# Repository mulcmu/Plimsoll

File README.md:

# Plimsoll

Prototype designs for klipper load cell ADC implementations.

### Alpha Test

STM32F072 and HX717 based strain gauge for use as a Klipper load cell.

Initial batch ordered for testing with JLCPCB.  About 5.5 USD cost per board.

Firmware and configuration tested with [current community test branch](https://github.com/garethky/klipper/tree/load-cell-probe-community-testing).

Smallish size, 20x50 mm footprint.  M2.5 mounting holes.  Fab house added the smaller tooling holes...

4 layer PCB all parts on top side.

MCU selected for crystal less USB operation with minimum of 64k flash for firmware.

Separate low noise, high PSRR for analog Vdd supply.

HX717 default data rate 320 Hz.  Adjustable with solder jumpers.

> [!NOTE]
>
> Crystal less main clock is problematic with Klipper and maybe the HX717 code.
>
> Works fine 90% of time, but suffers from occasional timeouts during probes.

### Mini HX717 / Mini ADS1220

Addon for a FYSETC H36 **v1** Toolhead board.  Uses the 2x6 2mm expansion pin headers for mounting.  Hardware spi works for the [H36_COMBO](https://wiki.fysetc.com/docs/H36-Combo).  The [H36_COMBO_V2](https://wiki.fysetc.com/docs/H36-Combo-V2) changed the header pins.

Straight needle 2mm 2x6 female pin header (4.3mm plastic body) fits with 6mm standoff but doesn't clear the _IO.0+1_ with a cable installed. A bent needle 2mm 2x6 header works (6mm plastic body) with 8mm standoff after bending the pins to be straight.

4 layer PCB all parts on top side.

Separate low noise, high PSRR for analog Vdd supply.

HX717 data rate 320 Hz.  

Klipper configs for ADS1220/HX717 configs.  
Users have reported __software SPI__ is functional on the v2 boards.

H36 V1
```
sensor_type: ads1220
cs_pin: toolhead:PB6
spi_bus: spi1a
data_ready_pin: toolhead:PC13

sensor_type: hx717
sclk_pin: toolhead:PB3
dout_pin: toolhead:PB4
```

H36 V2
```
sensor_type: ads1220
cs_pin: toolhead:PA14
data_ready_pin: toolhead:PA1
spi_software_sclk_pin:PB7
spi_software_mosi_pin:PB13
spi_software_miso_pin:PA15
spi_speed: 256000

sensor_type: hx717
sclk_pin: toolhead:PB7
dout_pin: toolhead:PA15
```

### 4ch Underbed

4 channel ADS131M04 for underbed applications.  Each load cell can be individually measured and digitally summed.

8.192 MHz clock hardware generator.

Separate low noise, high PSRR for analog Vdd supply.

### Todo:

- [X] Test 2mm pin header fitup on mini pcb
- [x] Test mini ads1220
- [x] Test mini hx717
- [ ] Test underbed pcb
- [ ] ADS131M04 firmware and klipper support

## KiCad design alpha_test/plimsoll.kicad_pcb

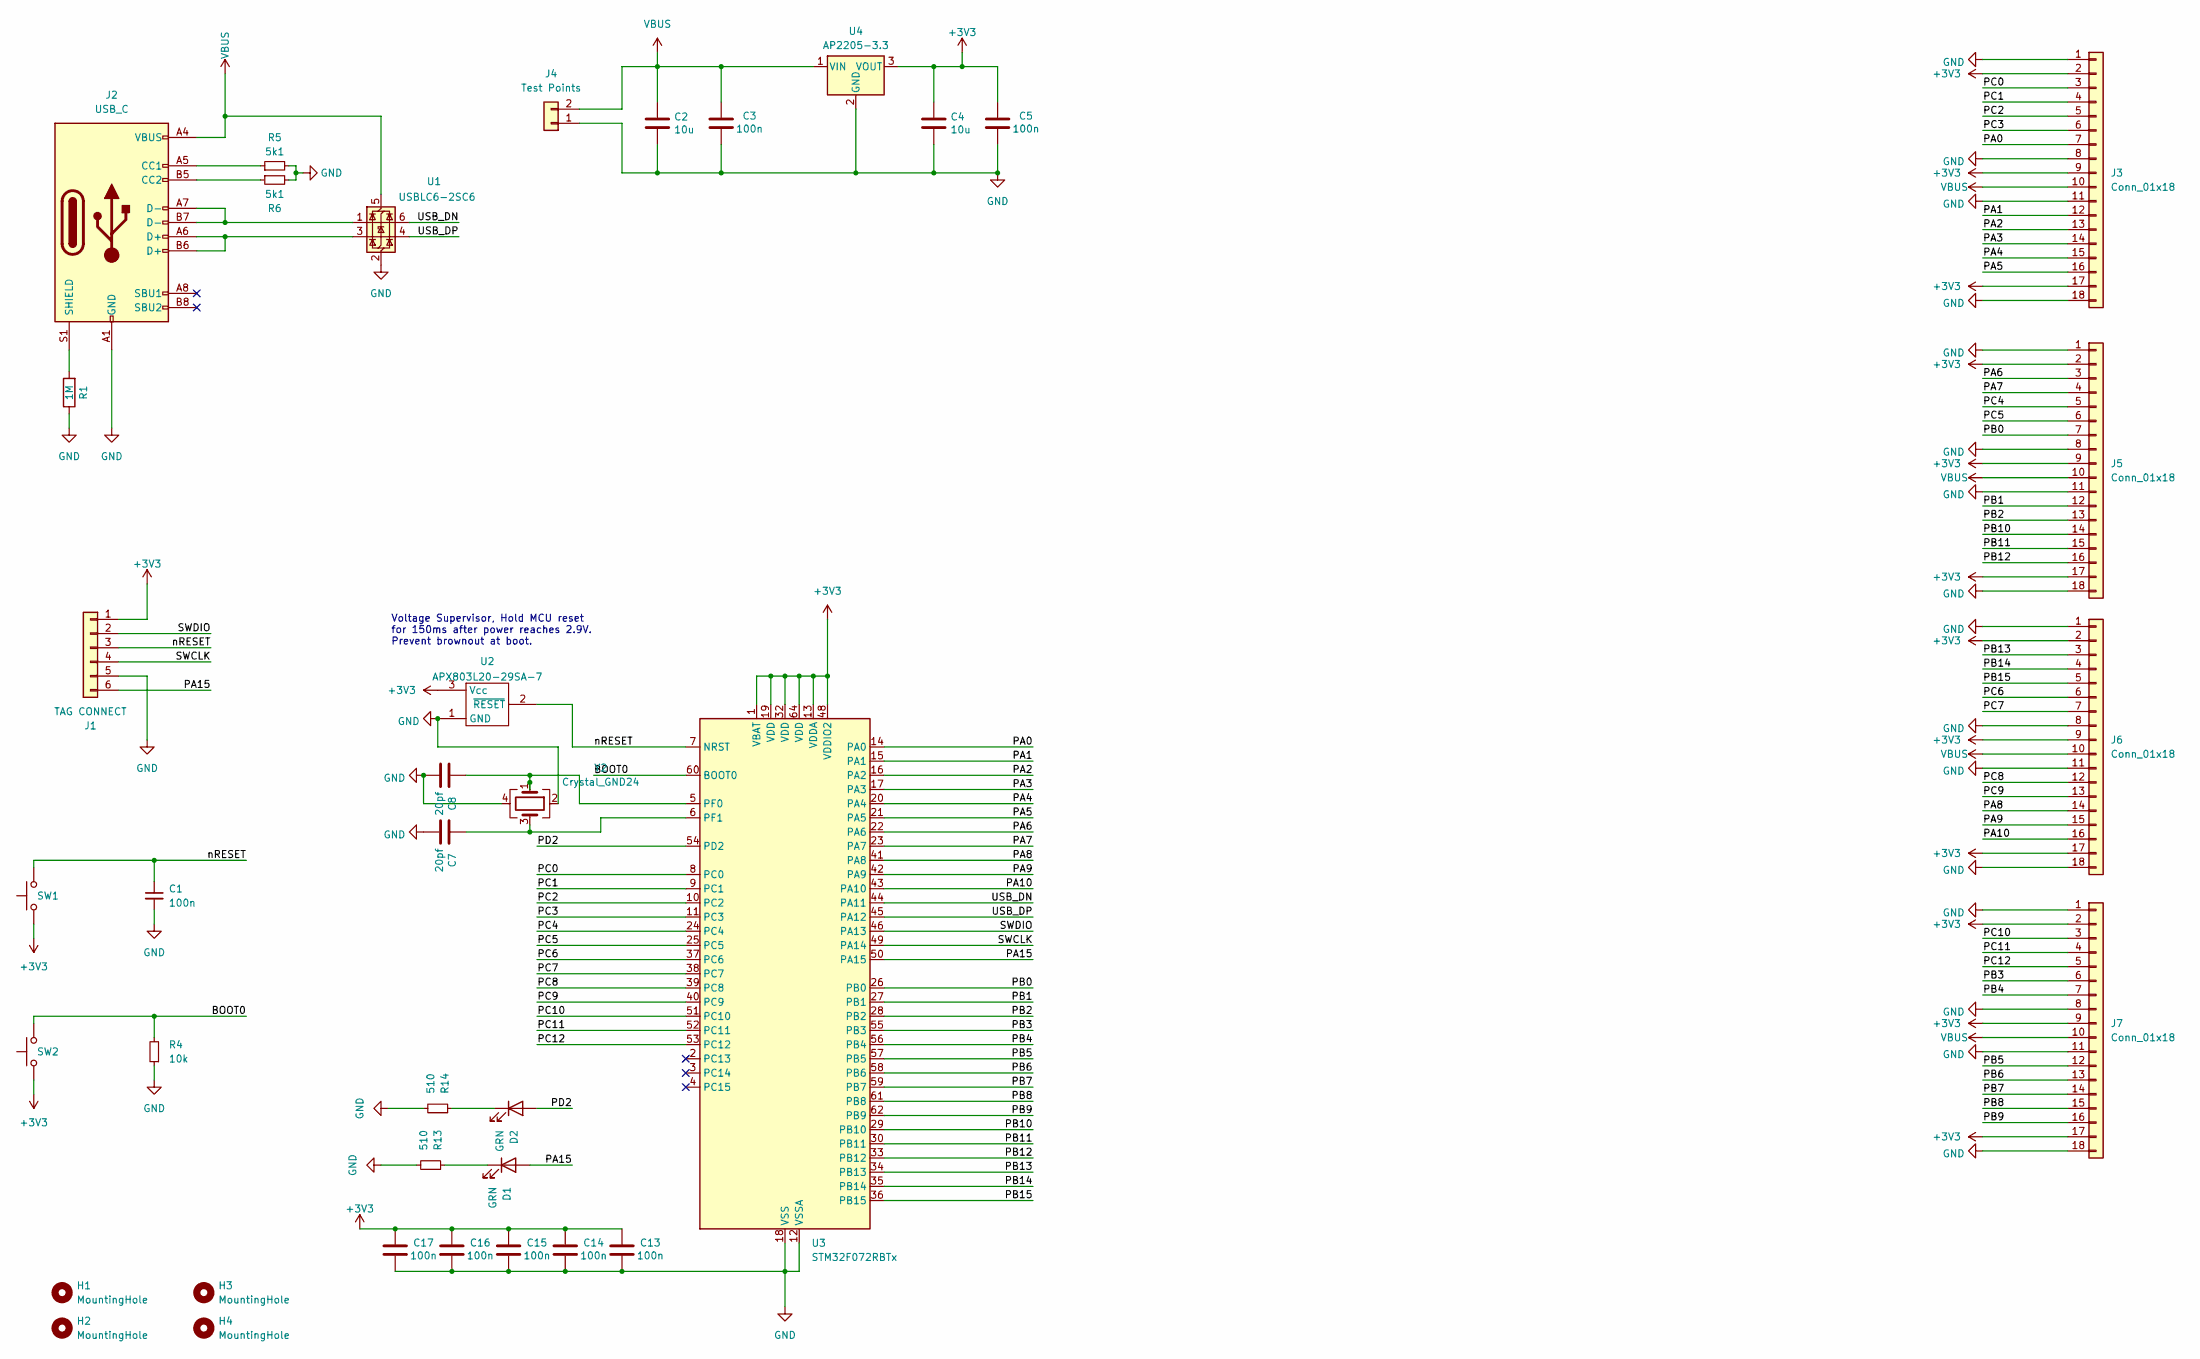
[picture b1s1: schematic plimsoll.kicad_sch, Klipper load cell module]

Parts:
C1, C3, C5, C13, C14, C15, C16, C17: 100n; C_0603_1608Metric; LCSC PN C14663
C2, C4: 10u; C_0805_2012Metric; LCSC PN C15850
C7, C8: 20pf; C_0603_1608Metric; LCSC PN C14663
D1, D2: GRN; LED_0805_2012Metric; LCSC PN C2297
H1, H2, H3, H4: MountingHole; MountingHole_2.2mm_M2_ISO7380
J1: TAG CONNECT; Tag-Connect_TC2030-IDC-NL_2x03_P1.27mm_Vertical
J2: USB_C; USB_C_Receptacle_G-Switch_GT-USB-7010ASV; LCSC PN C2988369
J3, J5, J6, J7: Conn_01x18; PinHeader_1x18_P2.54mm_Vertical
J4: Test Points; PinHeader_1x02_P2.54mm_Vertical
R1: 1M; R_0805_2012Metric; LCSC PN C17514
R4: 10k; R_0603_1608Metric; LCSC PN C25804
R5, R6: 5k1; R_0603_1608Metric; LCSC PN C23186
R13, R14: 510; R_0603_1608Metric; LCSC PN C23193
SW1: RESET; push_button; LCSC PN C720477
SW2: BOOT0; push_button; LCSC PN C720477
U1: USBLC6-2SC6; SOT-23-6; LCSC PN C7519
U2: APX803L20-29SA-7; SOT-23; LCSC PN C2067355
U3: STM32F072RBTx; LQFP-64_10x10mm_P0.5mm; LCSC PN C46046
U4: AP2205-3.3; SOT-89-3; LCSC PN C5205181
Y2: Crystal_GND24; Crystal_SMD_3225-4Pin_3.2x2.5mm_HandSoldering

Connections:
+3V3: C4.1, C5.2, C13.2, C14.2, C15.2, C16.2, C17.2, J1.1, J3.2, J3.9, J3.17, J5.2, J5.9, J5.17, J6.2, J6.9, J6.17, J7.2, J7.9, J7.17, SW1.1, SW2.1, U2.3 (Vcc), U3.1 (VBAT), U3.13 (VDDA), U3.19 (VDD), U3.32 (VDD), U3.48 (VDDIO2), U3.64 (VDD), U4.3 (VOUT); also elsewhere on the board
/BOOT0: R4.2, SW2.2, U3.60 (BOOT0); also elsewhere on the board
/PA0: J3.7, U3.14 (PA0)
/PA1: J3.12, U3.15 (PA1)
/PA2: J3.13, U3.16 (PA2)
/PA3: J3.14, U3.17 (PA3)
/PA4: J3.15, U3.20 (PA4)
/PA5: J3.16, U3.21 (PA5)
/PA6: J5.3, U3.22 (PA6)
/PA7: J5.4, U3.23 (PA7)
/PA8: J6.14, U3.41 (PA8)
/PA9: J6.15, U3.42 (PA9)
/PA10: J6.16, U3.43 (PA10)
/PA15: D1.2 (A), J1.6, U3.50 (PA15)
/PB0: J5.7, U3.26 (PB0)
/PB1: J5.12, U3.27 (PB1)
/PB2: J5.13, U3.28 (PB2)
/PB3: J7.6, U3.55 (PB3)
/PB4: J7.7, U3.56 (PB4)
/PB5: J7.12, U3.57 (PB5)
/PB6: J7.13, U3.58 (PB6)
/PB7: J7.14, U3.59 (PB7)
/PB8: J7.15, U3.61 (PB8)
/PB9: J7.16, U3.62 (PB9)
/PB10: J5.14, U3.29 (PB10)
/PB11: J5.15, U3.30 (PB11)
/PB12: J5.16, U3.33 (PB12)
/PB13: J6.3, U3.34 (PB13)
/PB14: J6.4, U3.35 (PB14)
/PB15: J6.5, U3.36 (PB15)
/PC0: J3.3, U3.8 (PC0)
/PC1: J3.4, U3.9 (PC1)
/PC2: J3.5, U3.10 (PC2)
/PC3: J3.6, U3.11 (PC3)
/PC4: J5.5, U3.24 (PC4)
/PC5: J5.6, U3.25 (PC5)
/PC6: J6.6, U3.37 (PC6)
/PC7: J6.7, U3.38 (PC7)
/PC8: J6.12, U3.39 (PC8)
/PC9: J6.13, U3.40 (PC9)
/PC10: J7.3, U3.51 (PC10)
/PC11: J7.4, U3.52 (PC11)
/PC12: J7.5, U3.53 (PC12)
/PD2: D2.2 (A), U3.54 (PD2)
/SWCLK: J1.4, U3.49 (PA14)
/SWDIO: J1.2, U3.46 (PA13)
/USB_DN: U1.6 (I/O1), U3.44 (PA11)
/USB_DP: U1.4 (I/O2), U3.45 (PA12)
/nRESET: C1.1, J1.3, SW1.2, U2.2 (~RESET), U3.7 (NRST); also elsewhere on the board
GND: C1.2, C2.2, C3.1, C4.2, C5.1, C7.1, C8.1, C13.1, C14.1, C15.1, C16.1, C17.1, J1.5, J2.A1 (GND), J2.A12 (GND), J2.B1 (GND), J2.B12 (GND), J3.1, J3.8, J3.11, J3.18, J4.1, J5.1, J5.8, J5.11, J5.18, J6.1, J6.8, J6.11, J6.18, J7.1, J7.8, J7.11, J7.18, R1.1, R4.1, R5.2, R6.2, R13.2, R14.2, U1.2 (GND), U2.1 (GND), U3.12 (VSSA), U3.18 (VSS), U3.31 (VSS), U3.47 (VSS), U3.63 (VSS), U4.2 (GND), Y2.2, Y2.4
unnamed: D1.1 (K), R13.1
unnamed: D2.1 (K), R14.1
unnamed: J2.A5 (CC1), R5.1
unnamed: J2.B5 (CC2), R6.1
unnamed: J2.A6 (D+), J2.B6 (D+), U1.3 (I/O2)
unnamed: J2.A7 (D-), J2.B7 (D-), U1.1 (I/O1)
unnamed: J2.S1 (SHIELD), R1.2
unnamed: C8.2, U3.5 (PF0), Y2.1
unnamed: C7.2, U3.6 (PF1), Y2.3
VBUS: C2.1, C3.2, J2.A4 (VBUS), J2.A9 (VBUS), J2.B4 (VBUS), J2.B9 (VBUS), J3.10, J4.2, J5.10, J6.10, J7.10, U1.5 (VBUS), U4.1 (VIN)

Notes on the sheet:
Voltage Supervisor, Hold MCU reset for 150ms after power reaches 2.9V. Prevent brownout at boot.

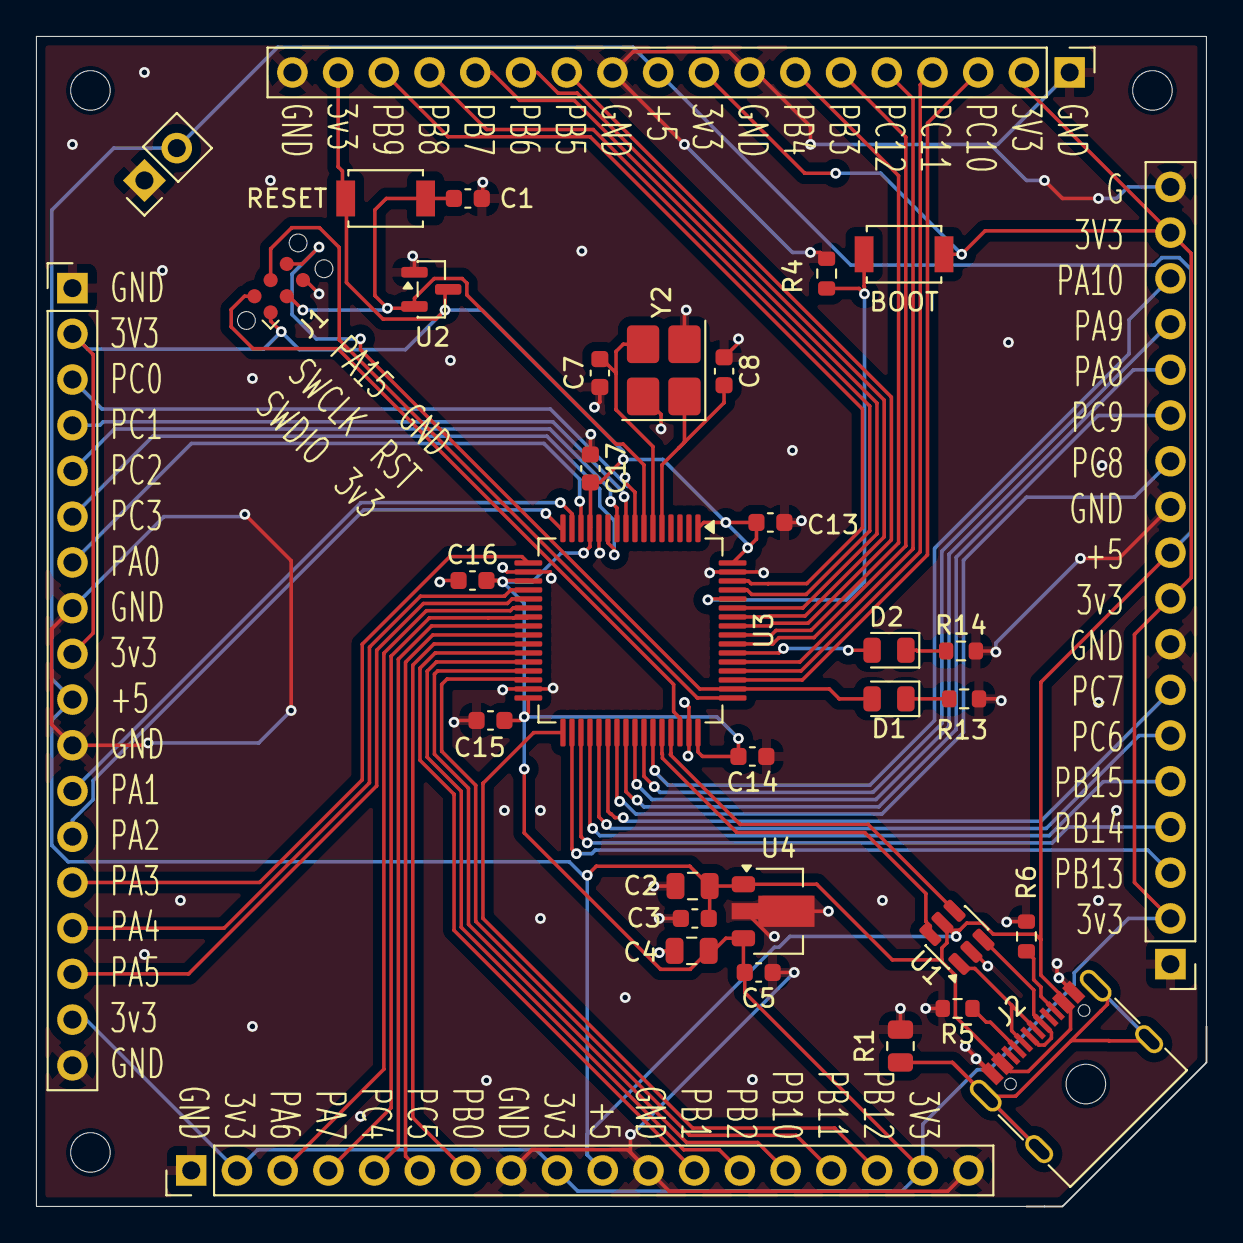
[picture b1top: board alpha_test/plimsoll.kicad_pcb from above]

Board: 4 copper layers, 65.0 x 65.0 mm, 38 parts (0 on the bottom side), 60 nets.

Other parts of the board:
BOOT: BOOT0; push_button
RESET: RESET; push_button

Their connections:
+3V3: BOOT.1, RESET.1; also elsewhere on the board
/BOOT0: BOOT.2; also elsewhere on the board
/nRESET: RESET.2; also elsewhere on the board

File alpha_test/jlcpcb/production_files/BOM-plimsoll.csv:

Comment,Designator,Footprint,LCSC,Quantity
100n,"C1,C13,C14,C15,C16,C17,C3,C5",C_0603_1608Metric,C14663,8
10k,R4,R_0603_1608Metric,C25804,1
10u,"C2,C4",C_0805_2012Metric,C15850,2
1M,R1,R_0805_2012Metric,C17514,1
20pf,"C7,C8",C_0603_1608Metric,C14663,2
510,"R13,R14",R_0603_1608Metric,C23193,2
5k1,"R5,R6",R_0603_1608Metric,C23186,2
AP2205-3.3,U4,SOT-89-3,C5205181,1
APX803L20-29SA-7,U2,SOT-23,C2067355,1
BOOT0,BOOT,push_button,C720477,1
GRN,"D1,D2",LED_0805_2012Metric,C2297,2
RESET,RESET,push_button,C720477,1
STM32F072RBTx,U3,LQFP-64_10x10mm_P0.5mm,C46046,1
USBLC6-2SC6,U1,SOT-23-6,C7519,1
USB_C,J2,USB_C_Receptacle_G-Switch_GT-USB-7010ASV,C2988369,1
Crystal_GND24,Y2,Crystal_SMD_3225-4Pin_3.2x2.5mm_HandSoldering,,1
Conn_01x18,J3,PinHeader_1x18_P2.54mm_Vertical,,1
Conn_01x18,J7,PinHeader_1x18_P2.54mm_Vertical,,1
Conn_01x18,J6,PinHeader_1x18_P2.54mm_Vertical,,1
Conn_01x18,J5,PinHeader_1x18_P2.54mm_Vertical,,1

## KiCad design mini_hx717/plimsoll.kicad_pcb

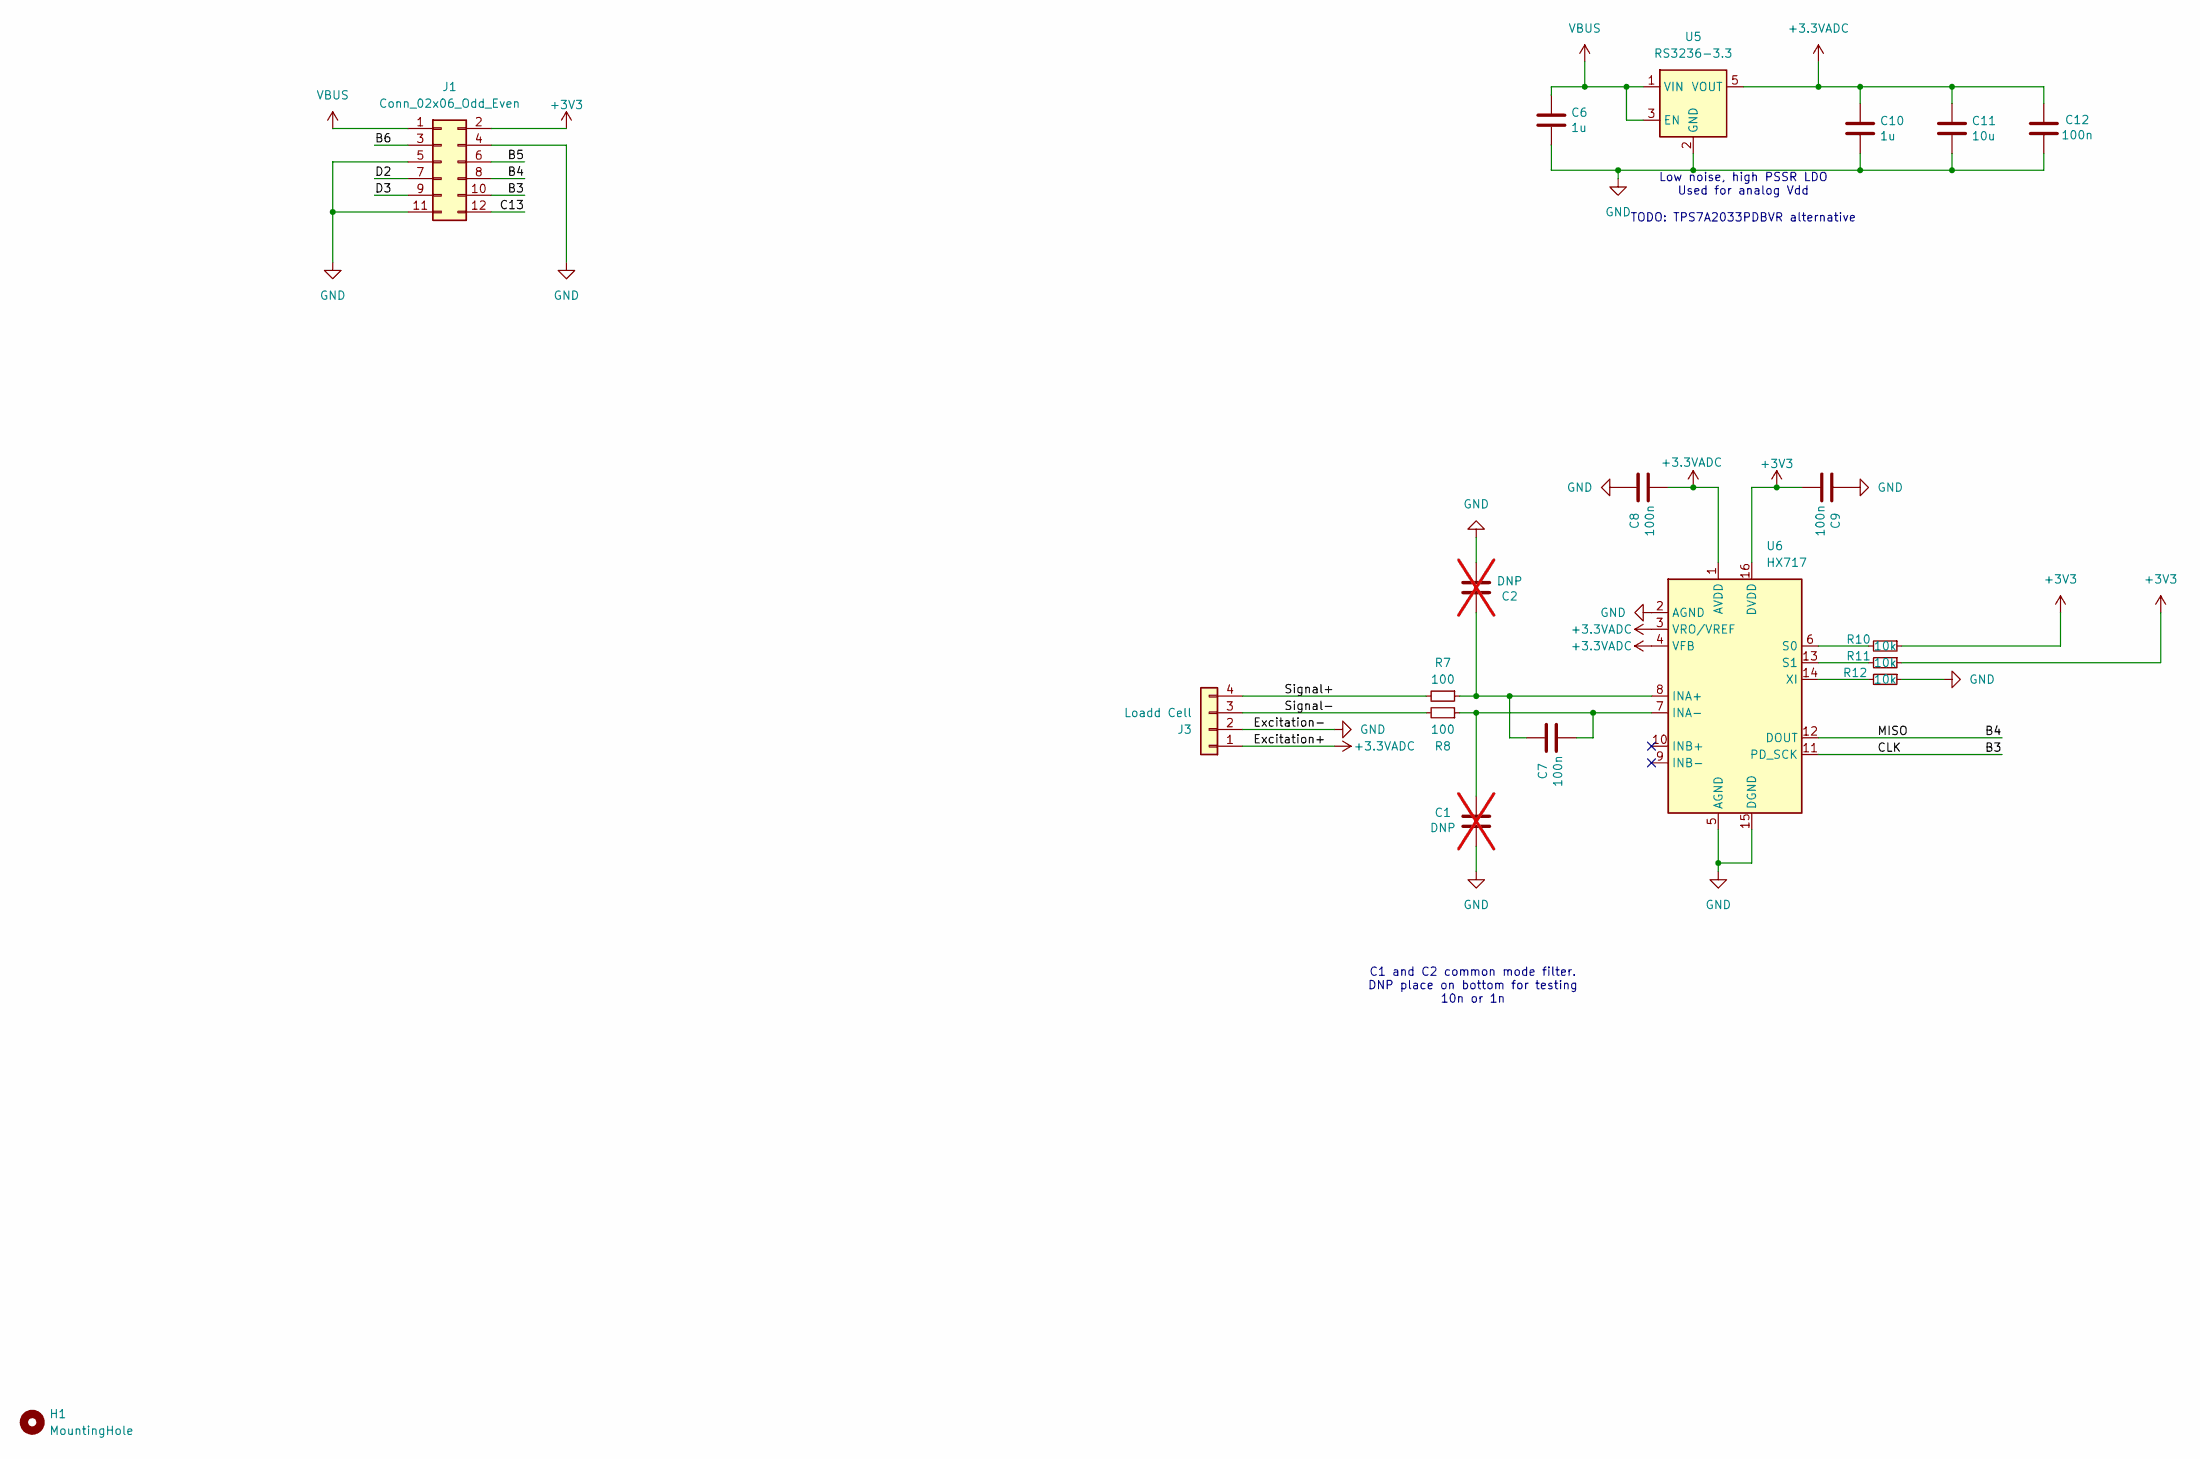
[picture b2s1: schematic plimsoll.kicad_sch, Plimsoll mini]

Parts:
C1, C2: DNP; C_0603_1608Metric; LCSC PN C14663; not fitted
C6, C10: 1u; C_0805_2012Metric; LCSC PN C28323
C7, C8, C9, C12: 100n; C_0603_1608Metric; LCSC PN C14663
C11: 10u; C_0805_2012Metric; LCSC PN C15850
H1: MountingHole; MountingHole_3.2mm_M3
J1: Conn_02x06_Odd_Even; PinSocket_2x06_P2.00mm_Vertical
J3: Loadd Cell; JST_XH_B4B-XH-A_1x04_P2.50mm_Vertical
R7, R8: 100; R_0603_1608Metric; LCSC PN C22775
R10, R11, R12: 10k; R_0603_1608Metric; LCSC PN C25804
U5: RS3236-3.3; SOT-23-5; LCSC PN C379349
U6: HX717; SOP-16_3.9x9.9mm_P1.27mm; LCSC PN C575394

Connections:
+3.3VADC: C8.1, C10.1, C11.1, C12.2, J3.1, U5.5 (VOUT), U6.1 (AVDD), U6.3 (VRO/VREF), U6.4 (VFB)
+3V3: C9.1, J1.2, R10.1, R11.1, U6.16 (DVDD)
/B3: J1.10, U6.11 (PD_SCK)
/B4: J1.8, U6.12 (DOUT)
/B5: J1.6
/B6: J1.3
/C13: J1.12
/D2: J1.7
/D3: J1.9
/Signal+: J3.4, R7.2
/Signal-: J3.3, R8.2
GND: C1.1, C2.1, C6.2, C8.2, C9.2, C10.2, C11.2, C12.1, J1.4, J1.5, J1.11, J3.2, R12.1, U5.2 (GND), U6.2 (AGND), U6.5 (AGND), U6.15 (DGND)
unnamed: C2.2, C7.2, R7.1, U6.8 (INA+)
unnamed: C1.2, C7.1, R8.1, U6.7 (INA-)
unnamed: R10.2, U6.6 (S0)
unnamed: R11.2, U6.13 (S1)
unnamed: R12.2, U6.14 (XI)
VBUS: C6.1, J1.1, U5.1 (VIN), U5.3 (EN)

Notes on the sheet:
C1 and C2 common mode filter. DNP place on bottom for testing 10n or 1n
Low noise, high PSSR LDO Used for analog Vdd TODO: TPS7A2033PDBVR alternative

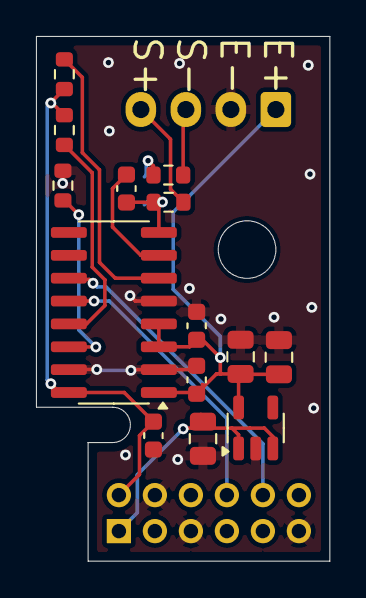
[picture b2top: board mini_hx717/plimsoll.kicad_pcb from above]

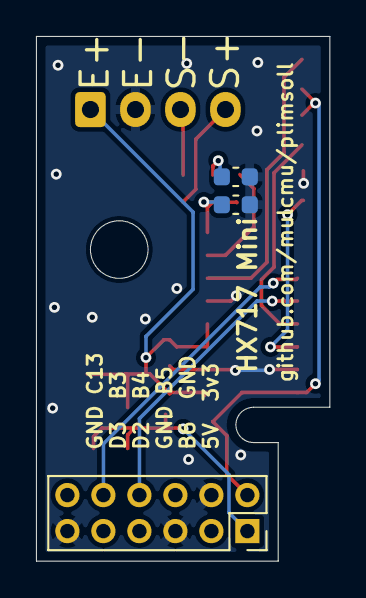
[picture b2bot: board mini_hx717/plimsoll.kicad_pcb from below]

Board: 4 copper layers, 16.3 x 29.1 mm, 19 parts (3 on the bottom side), 13 nets.

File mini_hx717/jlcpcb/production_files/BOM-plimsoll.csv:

Comment,Designator,Footprint,LCSC,Quantity
100,"R7,R8",R_0603_1608Metric,C22775,2
100n,"C12,C7,C8,C9",C_0603_1608Metric,C14663,4
10k,"R10,R11,R12",R_0603_1608Metric,C25804,3
10u,C11,C_0805_2012Metric,C15850,1
1u,"C10,C6",C_0805_2012Metric,C28323,2
HX717,U6,SOP-16_3.9x9.9mm_P1.27mm,C575394,1
RS3236-3.3,U5,SOT-23-5,C379349,1

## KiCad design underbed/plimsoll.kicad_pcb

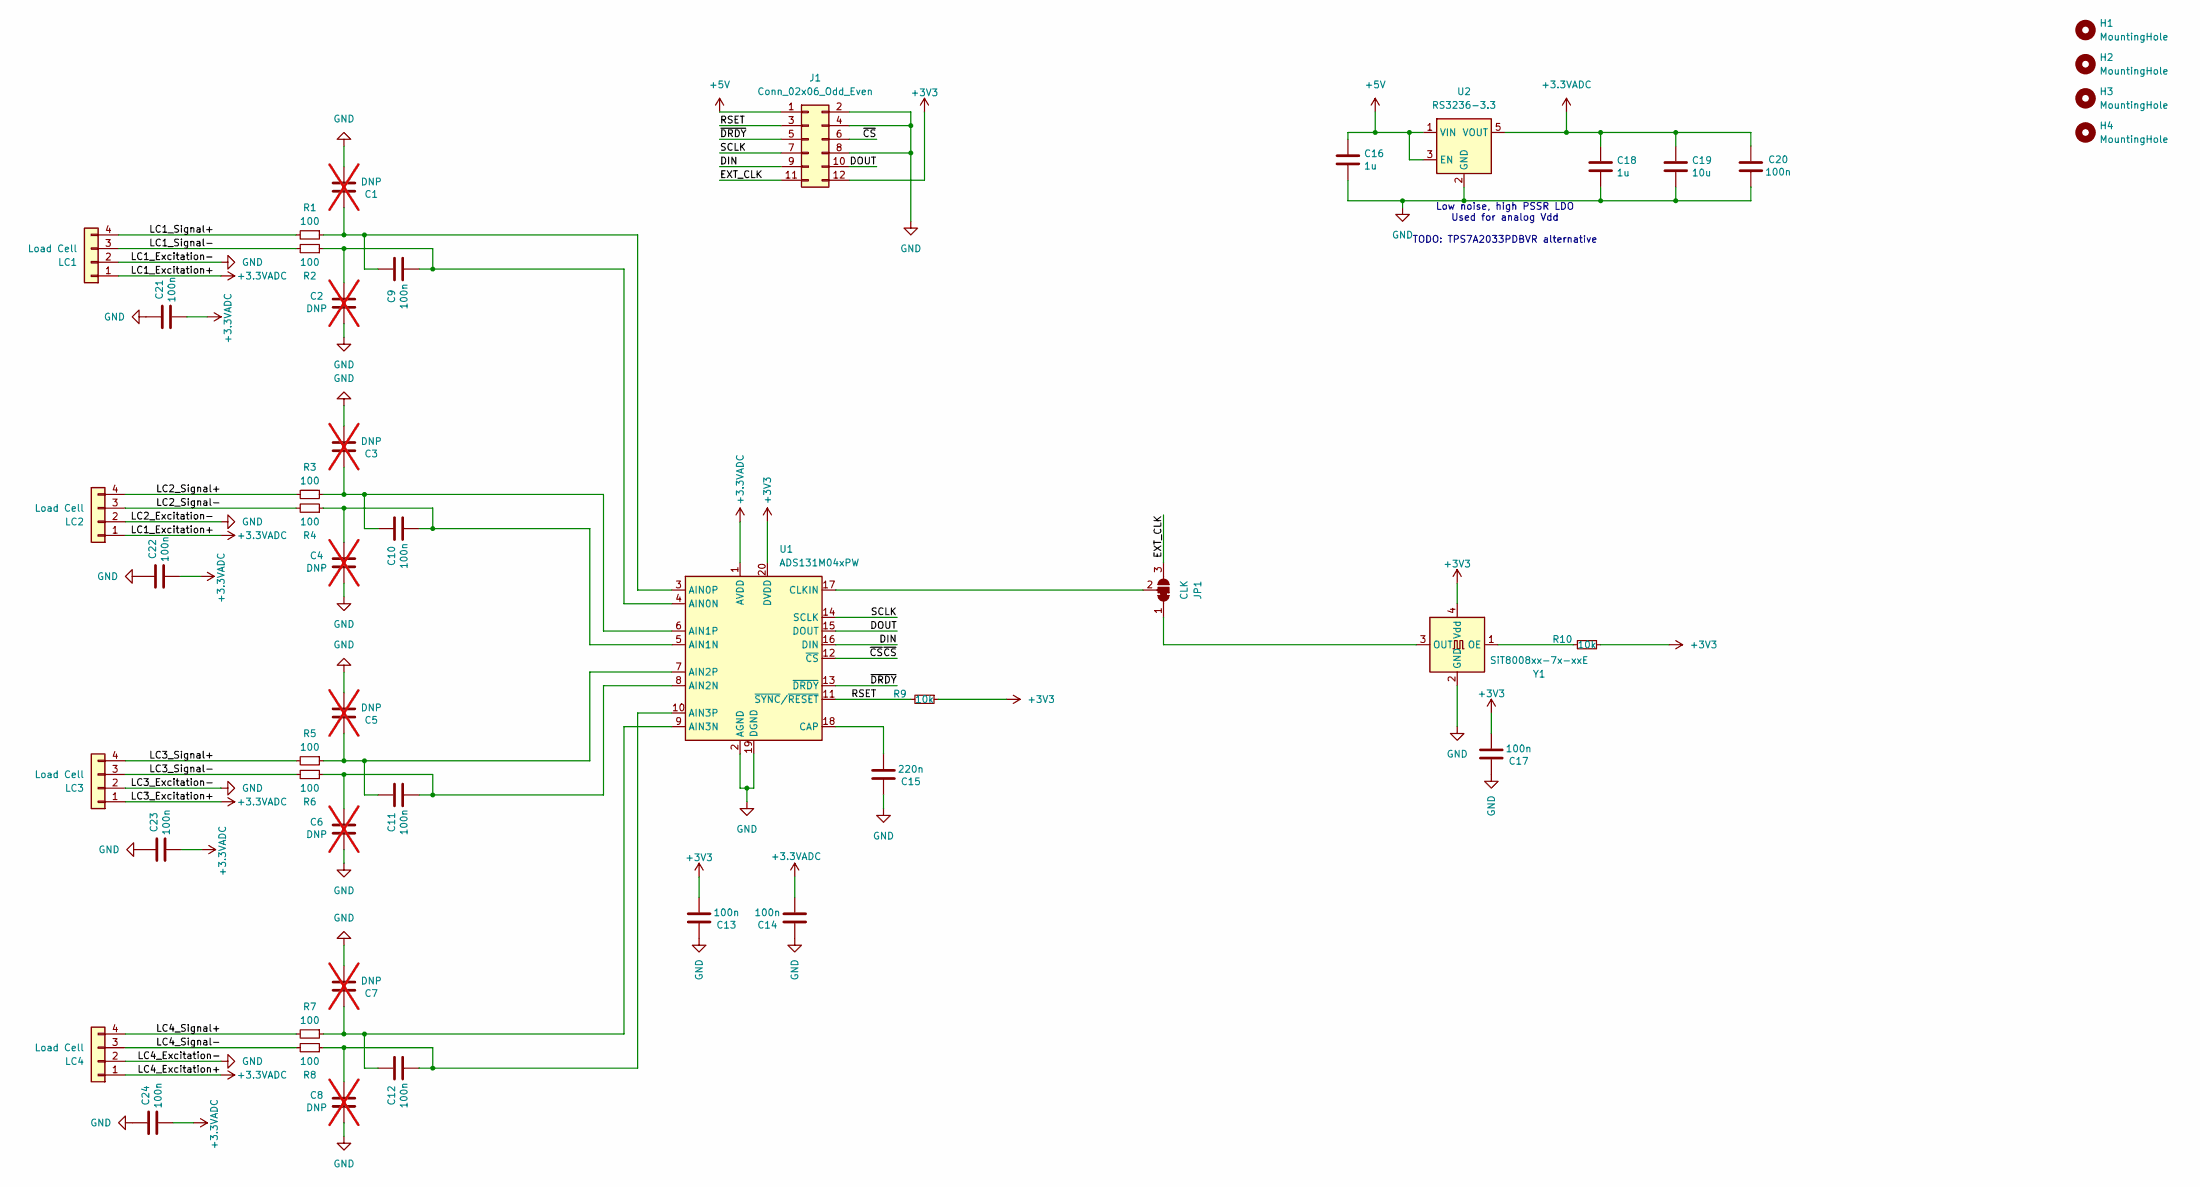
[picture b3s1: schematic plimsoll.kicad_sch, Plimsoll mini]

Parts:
C1, C2, C3, C4, C5, C6, C7, C8: DNP; C_0603_1608Metric; not fitted
C9, C10, C11, C12, C13, C14, C17, C20, C21, C22, C23, C24: 100n; C_0603_1608Metric; LCSC PN C14663
C15: 220n; C_0603_1608Metric; LCSC PN C21120
C16, C18: 1u; C_0805_2012Metric; LCSC PN C28323
C19: 10u; C_0805_2012Metric; LCSC PN C15850
H1, H2, H3, H4: MountingHole; MountingHole_3.2mm_M3
J1: Conn_02x06_Odd_Even; PinSocket_2x06_P2.54mm_Vertical
JP1: CLK; SolderJumper-3_P1.3mm_Bridged12_RoundedPad1.0x1.5mm_NumberL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
LC1, LC2, LC3, LC4: Load Cell; JST_XH_B4B-XH-A_1x04_P2.50mm_Vertical
R1, R2, R3, R4, R5, R6, R7, R8: 100; R_0603_1608Metric; LCSC PN C22775
R9, R10: 10k; R_0603_1608Metric; LCSC PN C25804
U1: ADS131M04xPW; TSSOP-20_4.4x6.5mm_P0.65mm; LCSC PN C2862562
U2: RS3236-3.3; SOT-23-5; LCSC PN C379349
Y1: SiT8008xx-7x-xxE; Oscillator_SMD_SiT_PQFN-4Pin_2.0x1.6mm; LCSC PN C347672

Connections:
+3.3VADC: C14.1, C18.1, C19.1, C20.2, C21.1, C22.1, C23.1, C24.1, LC1.1, LC2.1, LC3.1, LC4.1, U1.1 (AVDD), U2.5 (VOUT)
+3V3: C13.1, C17.1, J1.12, R9.1, R10.1, U1.20 (DVDD), Y1.4 (Vdd)
+5V: C16.1, J1.1, U2.1 (VIN), U2.3 (EN)
/DIN: J1.9, U1.16 (DIN)
/DOUT: J1.10, U1.15 (DOUT)
/EXT_CLK: J1.11, JP1.3 (B)
/LC1_Signal+: LC1.4, R1.2
/LC1_Signal-: LC1.3, R2.2
/LC2_Signal+: LC2.4, R3.2
/LC2_Signal-: LC2.3, R4.2
/LC3_Signal+: LC3.4, R5.2
/LC3_Signal-: LC3.3, R6.2
/LC4_Signal+: LC4.4, R7.2
/LC4_Signal-: LC4.3, R8.2
/RSET: J1.3, R9.2, U1.11 (~SYNC/~RESET)
/SCLK: J1.7, U1.14 (SCLK)
/~CS: J1.6, U1.12 (~CS)
/~DRDY: J1.5, U1.13 (~DRDY)
GND: C1.1, C2.1, C3.1, C4.1, C5.1, C6.1, C7.1, C8.1, C13.2, C14.2, C15.2, C16.2, C17.2, C18.2, C19.2, C20.1, C21.2, C22.2, C23.2, C24.2, J1.2, J1.4, J1.8, LC1.2, LC2.2, LC3.2, LC4.2, U1.2 (AGND), U1.19 (DGND), U2.2 (GND), Y1.2 (GND)
unnamed: JP1.1 (A), Y1.3 (OUT)
unnamed: JP1.2 (C), U1.17 (CLKIN)
unnamed: C2.2, C9.1, R2.1, U1.4 (AIN0N)
unnamed: C1.2, C9.2, R1.1, U1.3 (AIN0P)
unnamed: C4.2, C10.1, R4.1, U1.5 (AIN1N)
unnamed: C3.2, C10.2, R3.1, U1.6 (AIN1P)
unnamed: C6.2, C11.1, R6.1, U1.8 (AIN2N)
unnamed: C5.2, C11.2, R5.1, U1.7 (AIN2P)
unnamed: C7.2, C12.2, R7.1, U1.9 (AIN3N)
unnamed: C8.2, C12.1, R8.1, U1.10 (AIN3P)
unnamed: C15.1, U1.18 (CAP)
unnamed: R10.2, Y1.1 (OE)

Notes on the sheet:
Low noise, high PSSR LDO Used for analog Vdd TODO: TPS7A2033PDBVR alternative

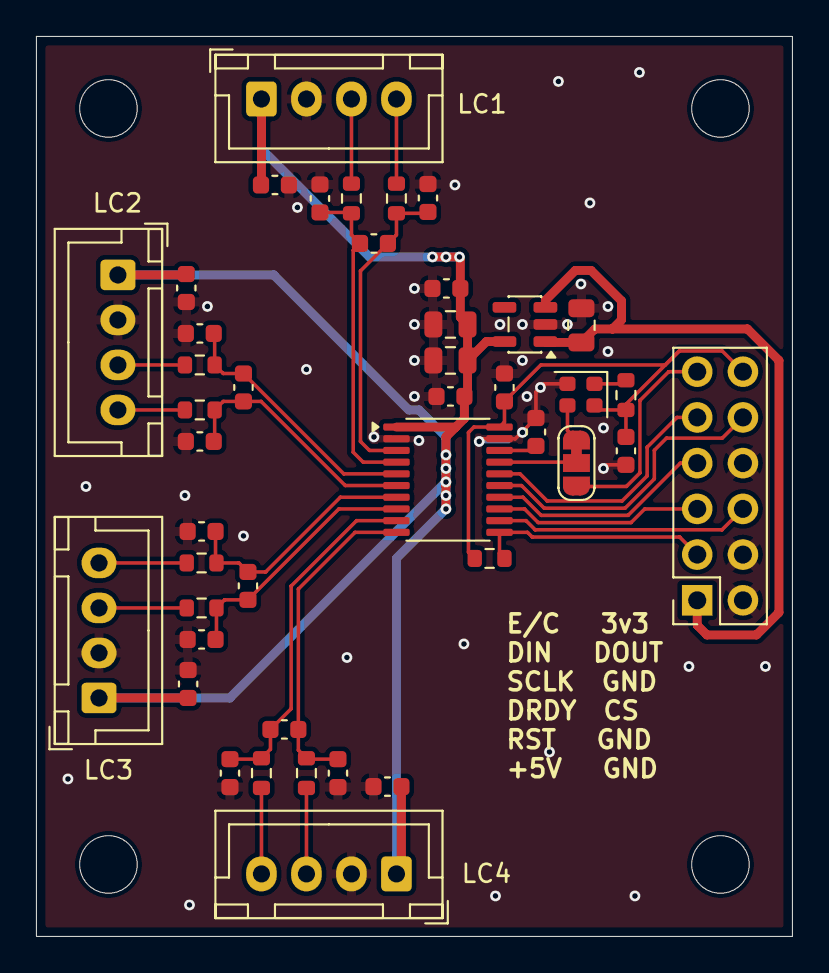
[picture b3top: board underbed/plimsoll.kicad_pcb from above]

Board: 4 copper layers, 42.0 x 50.0 mm, 47 parts (0 on the bottom side), 31 nets.

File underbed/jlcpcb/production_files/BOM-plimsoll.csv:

Comment,Designator,Footprint,LCSC,Quantity
100,"R1,R2,R3,R4,R5,R6,R7,R8",R_0603_1608Metric,C22775,8
100n,"C10,C11,C12,C13,C14,C17,C20,C21,C22,C23,C24,C9",C_0603_1608Metric,C14663,12
10k,"R10,R9",R_0603_1608Metric,C25804,2
10u,C19,C_0805_2012Metric,C15850,1
1u,"C16,C18",C_0805_2012Metric,C28323,2
220n,C15,C_0603_1608Metric,C21120,1
ADS131M04xPW,U1,TSSOP-20_4.4x6.5mm_P0.65mm,C2862562,1
RS3236-3.3,U2,SOT-23-5,C379349,1
SiT8008xx-7x-xxE,Y1,Oscillator_SMD_SiT_PQFN-4Pin_2.0x1.6mm,C347672,1

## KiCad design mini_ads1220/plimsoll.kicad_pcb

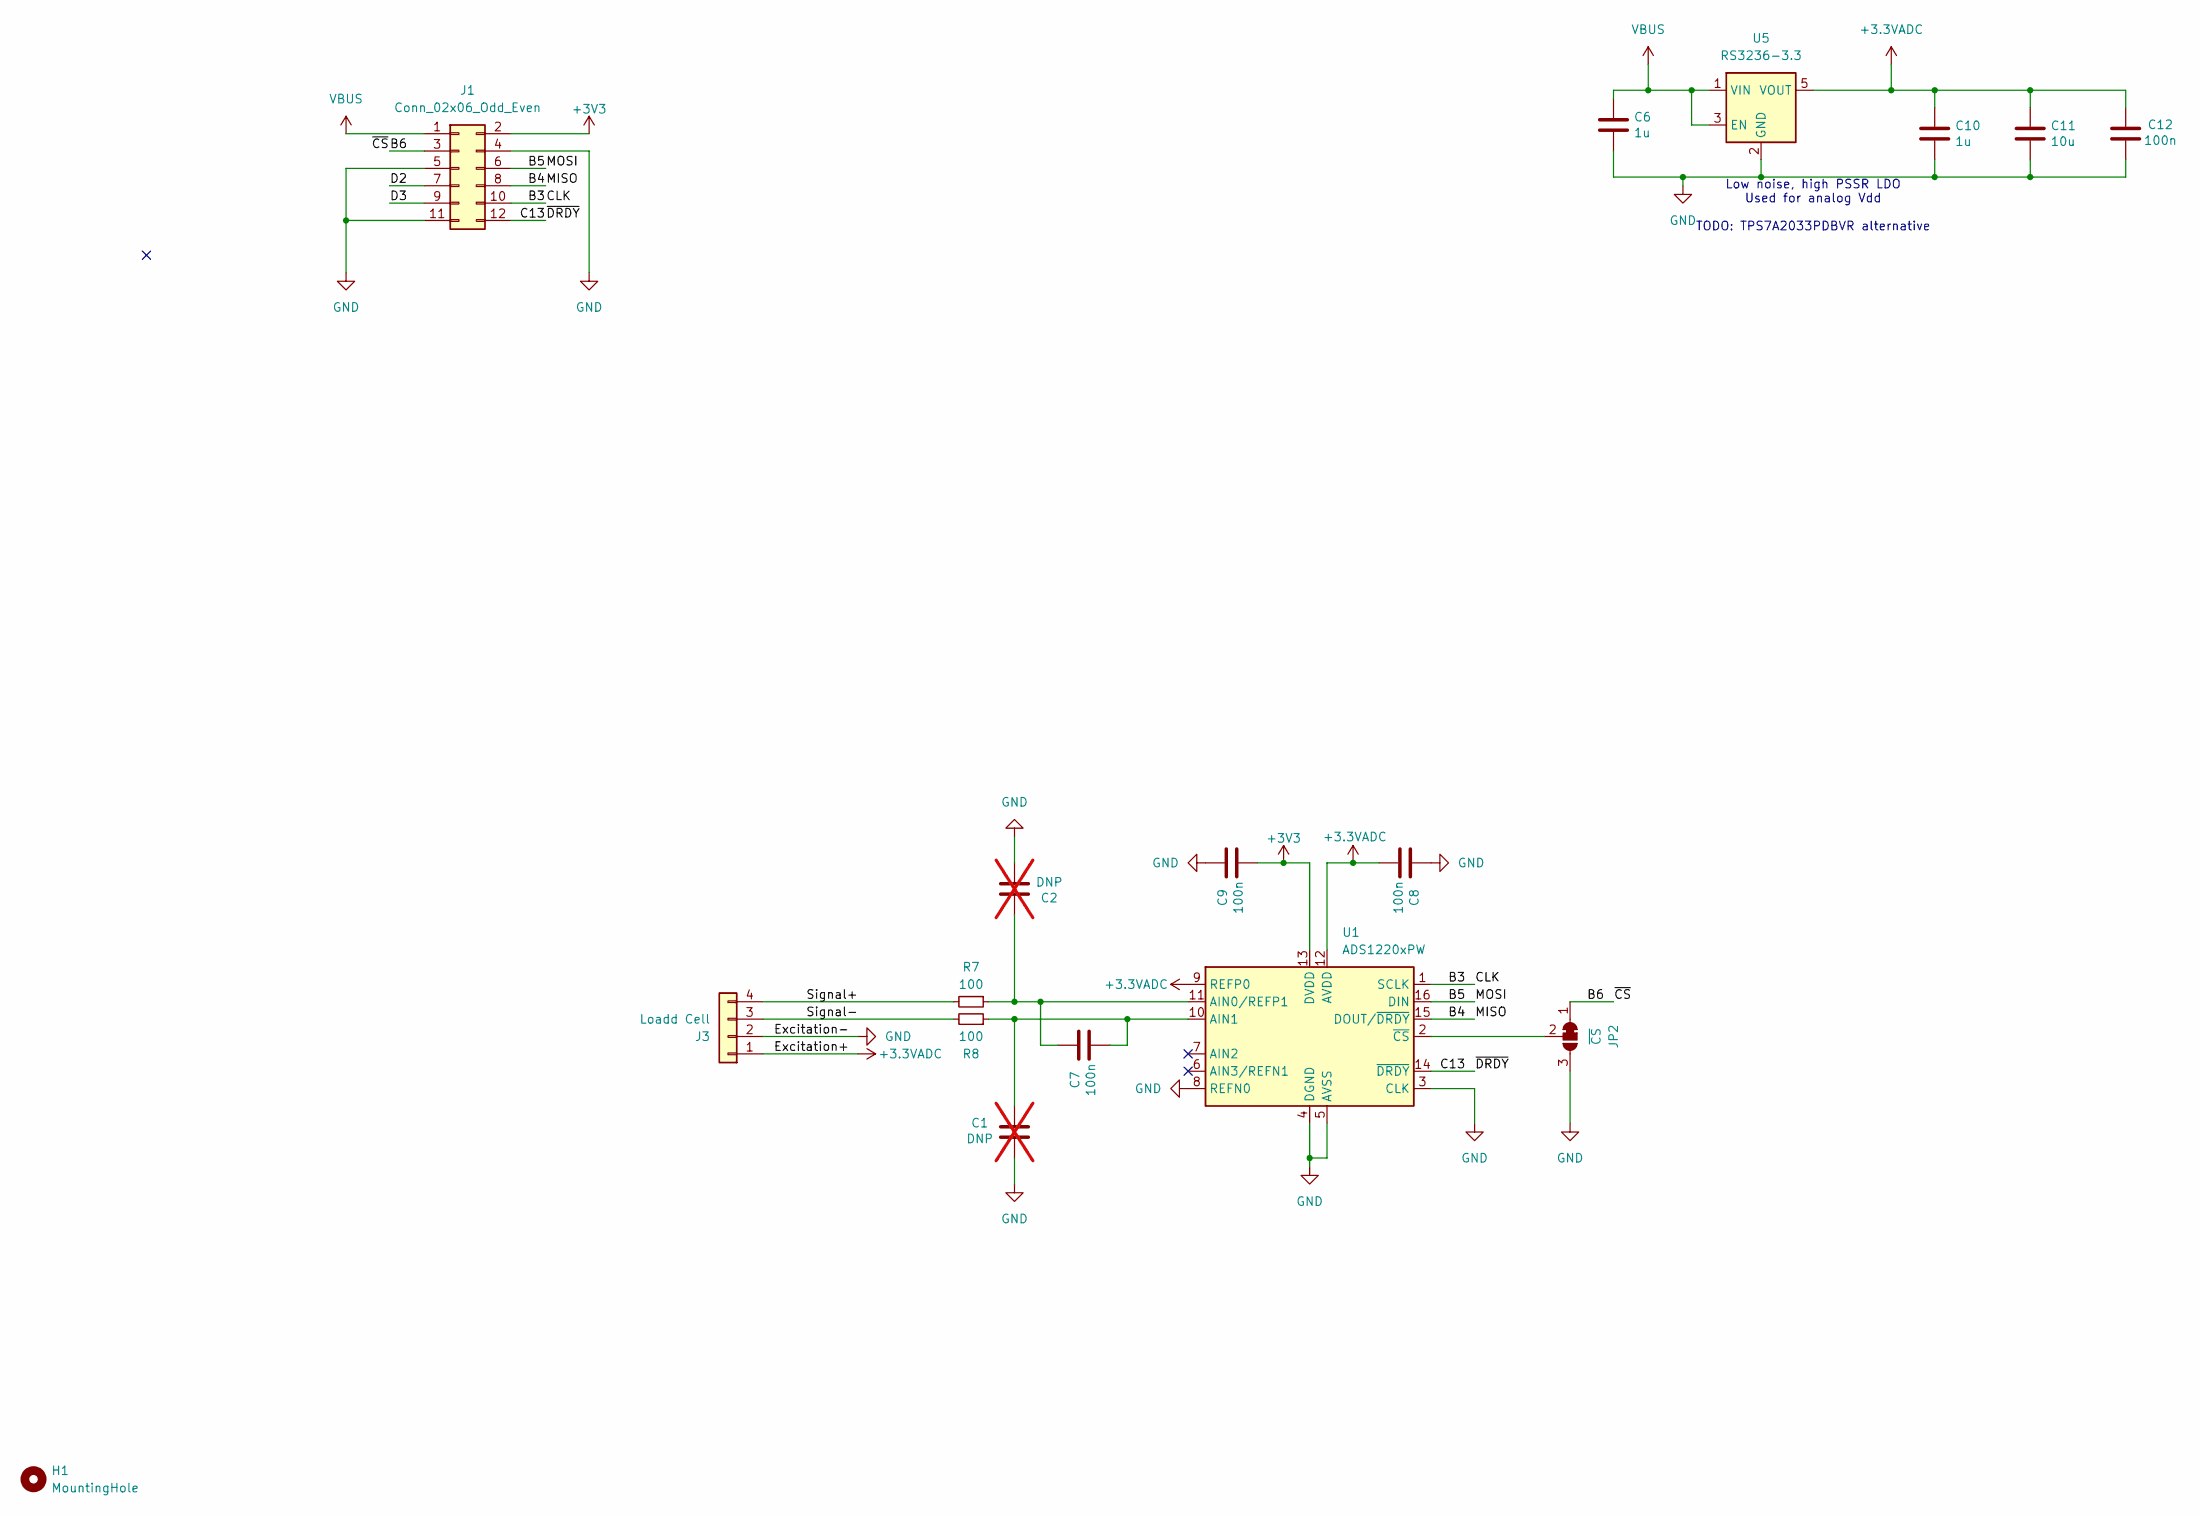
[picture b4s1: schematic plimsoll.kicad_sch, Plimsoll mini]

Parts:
C1, C2: DNP; C_0603_1608Metric; LCSC PN C14663; not fitted
C6, C10: 1u; C_0805_2012Metric; LCSC PN C28323
C7, C8, C9, C12: 100n; C_0603_1608Metric; LCSC PN C14663
C11: 10u; C_0805_2012Metric; LCSC PN C15850
H1: MountingHole; MountingHole_3.2mm_M3
J1: Conn_02x06_Odd_Even; PinSocket_2x06_P2.00mm_Vertical
J3: Loadd Cell; JST_XH_B4B-XH-A_1x04_P2.50mm_Vertical
JP2: ~{CS}; SolderJumper-3_P1.3mm_Bridged12_RoundedPad1.0x1.5mm_NumberL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
R7, R8: 100; R_0603_1608Metric; LCSC PN C22775
U1: ADS1220xPW; TSSOP-16_4.4x5mm_P0.65mm
U5: RS3236-3.3; SOT-23-5; LCSC PN C379349

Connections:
+3.3VADC: C8.1, C10.1, C11.1, C12.2, J3.1, U1.9 (REFP0), U1.12 (AVDD), U5.5 (VOUT)
+3V3: C9.1, J1.2, U1.13 (DVDD)
/B3: J1.10, U1.1 (SCLK)
/B4: J1.8, U1.15 (DOUT/~DRDY)
/B5: J1.6, U1.16 (DIN)
/B6: J1.3, JP2.1 (A)
/C13: J1.12, U1.14 (~DRDY)
/D2: J1.7
/D3: J1.9
/Signal+: J3.4, R7.2
/Signal-: J3.3, R8.2
GND: C1.1, C2.1, C6.2, C8.2, C9.2, C10.2, C11.2, C12.1, J1.4, J1.5, J1.11, J3.2, JP2.3 (B), U1.3 (CLK), U1.4 (DGND), U1.5 (AVSS), U1.8 (REFN0), U5.2 (GND)
unnamed: JP2.2 (C), U1.2 (~CS)
unnamed: C2.2, C7.2, R7.1, U1.11 (AIN0/REFP1)
unnamed: C1.2, C7.1, R8.1, U1.10 (AIN1)
VBUS: C6.1, J1.1, U5.1 (VIN), U5.3 (EN)

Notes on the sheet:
Low noise, high PSSR LDO Used for analog Vdd TODO: TPS7A2033PDBVR alternative

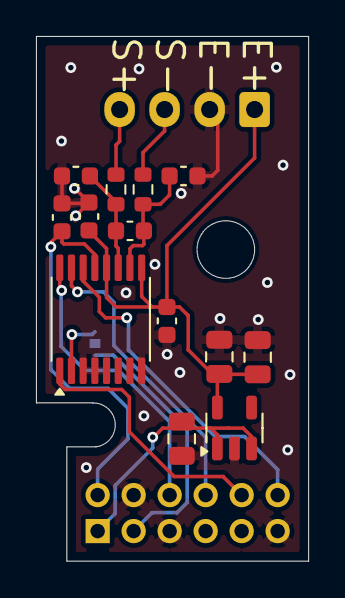
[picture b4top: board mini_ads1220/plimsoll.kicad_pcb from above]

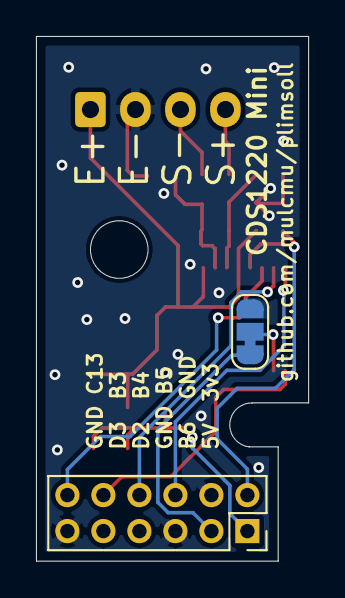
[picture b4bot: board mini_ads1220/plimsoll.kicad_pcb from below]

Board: 4 copper layers, 15.1 x 29.1 mm, 17 parts (2 on the bottom side), 14 nets.

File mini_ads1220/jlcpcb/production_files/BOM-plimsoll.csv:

Comment,Designator,Footprint,LCSC,Quantity
100,"R7,R8",R_0603_1608Metric,C22775,2
100n,"C12,C7,C8,C9",C_0603_1608Metric,C14663,4
10u,C11,C_0805_2012Metric,C15850,1
1u,"C10,C6",C_0805_2012Metric,C28323,2
ADS1220xPW,U1,TSSOP-16_4.4x5mm_P0.65mm,C48263,1
RS3236-3.3,U5,SOT-23-5,C379349,1

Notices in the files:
alpha_test/plimsoll.kicad_sch:
CERN-OHL-S
